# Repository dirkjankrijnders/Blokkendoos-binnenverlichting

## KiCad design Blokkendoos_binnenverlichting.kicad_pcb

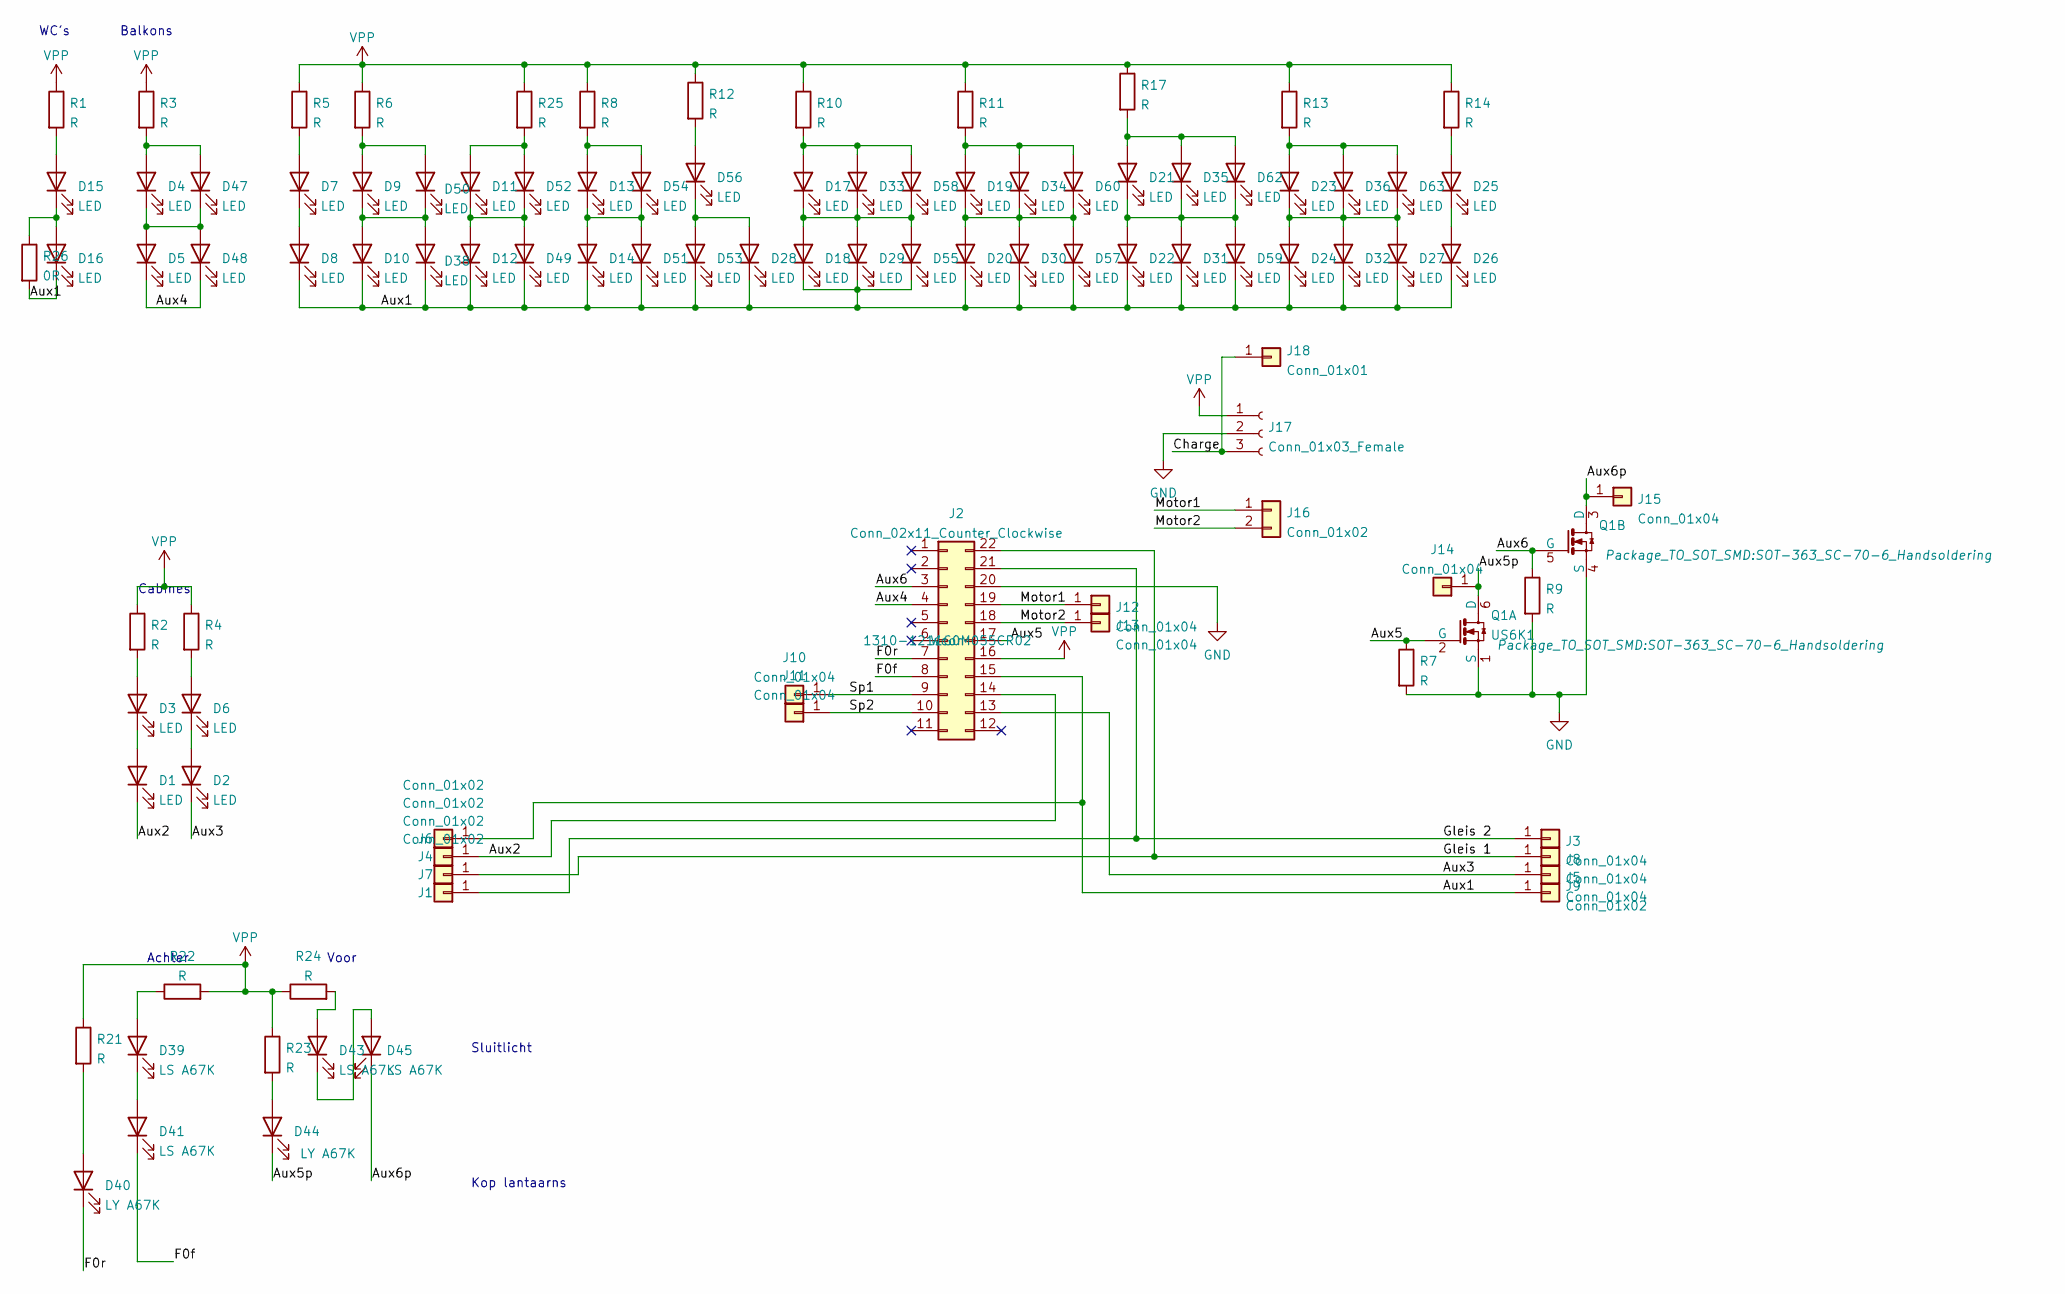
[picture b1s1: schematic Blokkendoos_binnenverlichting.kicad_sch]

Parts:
D1, D2, D3, D4, D5, D6, D7, D8, D9, D10, D11, D12, D13, D14, D15, D16, D17, D18, D19, D20, D21, D22, D23, D24, D25, D26, D27, D28, D29, D30, D31, D32, D33, D34, D35, D36, D38, D47, D48, D49, D50, D51, D52, D53, D54, D55, D56, D57, D58, D59, D60, D62, D63: LED; MHT151CYCT
D39, D41, D43, D45: LS A67K; LED_Osram_LY_A64K; MPN LS A67K-J1L2-1-0-2-R33-Z; LCSC C2830540
D40, D44: LY A67K; LED_Osram_LY_A64K; MPN LY A67K-J2M1-26-0-2-R33-Z; LCSC C2900136
J1, J4, J6, J7, J9: Conn_01x02; TestPoint_Pad_1.0x1.0mm
J2: Conn_02x11_Counter_Clockwise; PinHeader_2x11_P1.27mm_Vertical_SMD; LCSC C920913
J3, J5, J8, J10, J11, J12, J13, J14, J15: Conn_01x04; TestPoint_Pad_1.0x1.0mm
J16: Conn_01x02; Blokkendoos motor spings
J17: Conn_01x03_Female; PinHeader_1x03_P2.54mm_Horizontal
J18: Conn_01x01; PinHeader_1x01_P2.54mm_Horizontal
Q1: US6K1; SOT-363_SC-70-6_Handsoldering; LCSC2 C703686
R1, R2, R3, R4, R5, R6, R7, R8, R9, R10, R11, R12, R13, R14, R17, R21, R22, R23, R24, R25: R; R_0805_2012Metric_Pad1.20x1.40mm_HandSolder
R26: 0R; R_0805_2012Metric_Pad1.20x1.40mm_HandSolder

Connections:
/Aux1: D8.1 (K), D10.1 (K), D12.1 (K), D14.1 (K), D16.1 (K), D18.1 (K), D20.1 (K), D22.1 (K), D24.1 (K), D26.1 (K), D27.1 (K), D28.1 (K), D29.1 (K), D30.1 (K), D31.1 (K), D32.1 (K), D38.1 (K), D49.1 (K), D51.1 (K), D53.1 (K), D55.1 (K), D57.1 (K), D59.1 (K), J2.15, J6.1, J9.1, R26.2
/Aux2: D1.1 (K), J2.14, J4.1
/Aux3: D2.1 (K), J2.13, J5.1
/Aux4: D5.1 (K), D48.1 (K), J2.4
/Aux5: J2.17, Q1.2 (G), R7.1
/Aux5p: D44.1 (K), J14.1, Q1.6 (D)
/Aux6: J2.3, Q1.5 (G), R9.1
/Aux6p: D45.1 (K), J15.1, Q1.3 (D)
/Charge: J17.3, J18.1
/F0f: D41.1 (K), J2.8
/F0r: D40.1 (K), J2.7
/Gleis 1: J2.22, J7.1, J8.1
/Gleis 2: J1.1, J2.21, J3.1
/Motor1: J2.19, J12.1, J16.1
/Motor2: J2.18, J13.1, J16.2
/Sp1: J2.9, J10.1
/Sp2: J2.10, J11.1
GND: J2.20, J17.2, Q1.1 (S), Q1.4 (S), R7.2, R9.2
unnamed: D1.2 (A), D3.1 (K)
unnamed: D2.2 (A), D6.1 (K)
unnamed: D3.2 (A), R2.2
unnamed: D4.1 (K), D5.2 (A), D47.1 (K), D48.2 (A)
unnamed: D4.2 (A), D47.2 (A), R3.2
unnamed: D6.2 (A), R4.2
unnamed: D7.1 (K), D8.2 (A)
unnamed: D7.2 (A), R5.2
unnamed: D9.1 (K), D10.2 (A), D38.2 (A), D50.1 (K)
unnamed: D11.1 (K), D12.2 (A), D49.2 (A), D52.1 (K)
unnamed: D11.2 (A), D52.2 (A), R25.2
unnamed: D13.1 (K), D14.2 (A), D51.2 (A), D54.1 (K)
unnamed: D13.2 (A), D54.2 (A), R8.2
unnamed: D15.1 (K), D16.2 (A), R26.1
unnamed: D15.2 (A), R1.2
unnamed: D17.1 (K), D18.2 (A), D29.2 (A), D33.1 (K), D55.2 (A), D58.1 (K)
unnamed: D17.2 (A), D33.2 (A), D58.2 (A), R10.2
unnamed: D19.1 (K), D20.2 (A), D30.2 (A), D34.1 (K), D57.2 (A), D60.1 (K)
unnamed: D19.2 (A), D34.2 (A), D60.2 (A), R11.2
unnamed: D21.1 (K), D22.2 (A), D31.2 (A), D35.1 (K), D59.2 (A), D62.1 (K)
unnamed: D21.2 (A), D35.2 (A), D62.2 (A), R17.2
unnamed: D23.1 (K), D24.2 (A), D27.2 (A), D32.2 (A), D36.1 (K), D63.1 (K)
unnamed: D23.2 (A), D36.2 (A), D63.2 (A), R13.2
unnamed: D25.1 (K), D26.2 (A)
unnamed: D25.2 (A), R14.2
unnamed: D28.2 (A), D53.2 (A), D56.1 (K)
unnamed: D39.1 (K), D41.2 (A)
unnamed: D39.2 (A), R22.1
unnamed: D40.2 (A), R21.2
unnamed: D43.1 (K), D45.2 (A)
unnamed: D43.2 (A), R24.2
unnamed: D44.2 (A), R23.2
unnamed: D9.2 (A), D50.2 (A), R6.2
unnamed: D56.2 (A), R12.2
VPP: J2.16, J17.1, R1.1, R2.1, R3.1, R4.1, R5.1, R6.1, R8.1, R10.1, R11.1, R12.1, R13.1, R14.1, R17.1, R21.1, R22.2, R23.1, R24.1, R25.1

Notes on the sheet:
Sluitlicht
Kop lantaarns
Achter
WC's
Balkons
Cabines
Voor

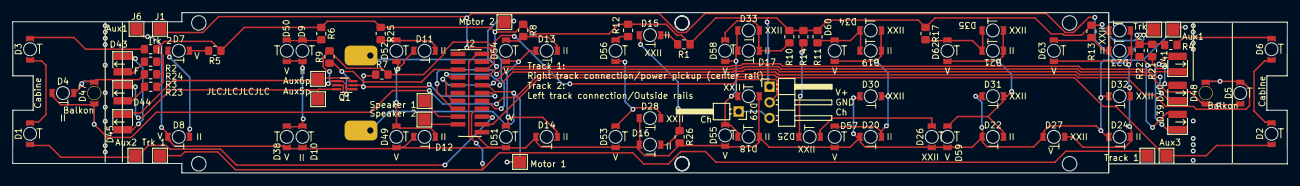
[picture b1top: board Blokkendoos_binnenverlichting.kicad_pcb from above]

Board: 2 copper layers, 206.8 x 26.0 mm, 99 parts (0 on the bottom side), 53 nets.

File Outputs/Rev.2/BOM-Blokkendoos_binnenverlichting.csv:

Comment,Designator,Footprint,LCSC
LS A67K,"D39,D41,D43,D45",LED_Osram_LY_A64K,C2830540
US6K1,Q1,SOT-363_SC-70-6_Handsoldering,C703686
Conn_02x11_Counter_Clockwise,J2,PinHeader_2x11_P1.27mm_Vertical_SMD,C920913
LED,D13,MHT151CYCT,
R,R21,R_0805_2012Metric_Pad1.20x1.40mm_HandSolder,
LED,D19,MHT151CYCT,
R,R12,R_0805_2012Metric_Pad1.20x1.40mm_HandSolder,
LED,D10,MHT151CYCT,
R,R7,R_0805_2012Metric_Pad1.20x1.40mm_HandSolder,
LED,D51,MHT151CYCT,
LED,D38,MHT151CYCT,
Conn_01x03_Female,J17,PinHeader_1x03_P2.54mm_Horizontal,
LED,D17,MHT151CYCT,
R,R2,R_0805_2012Metric_Pad1.20x1.40mm_HandSolder,
LED,D32,MHT151CYCT,
LED,D9,MHT151CYCT,
R,R23,R_0805_2012Metric_Pad1.20x1.40mm_HandSolder,
LED,D27,MHT151CYCT,
LED,D18,MHT151CYCT,
R,R1,R_0805_2012Metric_Pad1.20x1.40mm_HandSolder,
LED,D14,MHT151CYCT,
LED,D6,MHT151CYCT,
LED,D36,MHT151CYCT,
LY A67K,D40,LED_Osram_LY_A64K,
Conn_01x02,J16,Blokkendoos motor spings,
R,R5,R_0805_2012Metric_Pad1.20x1.40mm_HandSolder,
0R,R26,R_0805_2012Metric_Pad1.20x1.40mm_HandSolder,
R,R4,R_0805_2012Metric_Pad1.20x1.40mm_HandSolder,
LED,D24,MHT151CYCT,
LED,D62,MHT151CYCT,
LED,D12,MHT151CYCT,
LED,D33,MHT151CYCT,
LED,D22,MHT151CYCT,
LED,D3,MHT151CYCT,
LED,D8,MHT151CYCT,
LED,D28,MHT151CYCT,
LED,D31,MHT151CYCT,
R,R25,R_0805_2012Metric_Pad1.20x1.40mm_HandSolder,
LED,D49,MHT151CYCT,
R,R8,R_0805_2012Metric_Pad1.20x1.40mm_HandSolder,
LED,D63,MHT151CYCT,
LED,D11,MHT151CYCT,
LED,D60,MHT151CYCT,
LED,D34,MHT151CYCT,
R,R6,R_0805_2012Metric_Pad1.20x1.40mm_HandSolder,
LED,D57,MHT151CYCT,
LED,D30,MHT151CYCT,
R,R22,R_0805_2012Metric_Pad1.20x1.40mm_HandSolder,
LED,D5,MHT151CYCT,
LED,D25,MHT151CYCT,
LED,D1,MHT151CYCT,
LED,D4,MHT151CYCT,
LED,D21,MHT151CYCT,
LED,D20,MHT151CYCT,
LED,D53,MHT151CYCT,
R,R3,R_0805_2012Metric_Pad1.20x1.40mm_HandSolder,
LED,D47,MHT151CYCT_dual_side,
Conn_01x01,J18,PinHeader_1x01_P2.54mm_Horizontal,
LED,D48,MHT151CYCT_dual_side,
R,R9,R_0805_2012Metric_Pad1.20x1.40mm_HandSolder,
LED,D50,MHT151CYCT,
LED,D26,MHT151CYCT,
LED,D35,MHT151CYCT,
LY A67K,D44,LED_Osram_LY_A64K,
LED,D52,MHT151CYCT,
LED,D2,MHT151CYCT,
LED,D7,MHT151CYCT,
R,R11,R_0805_2012Metric_Pad1.20x1.40mm_HandSolder,
LED,D23,MHT151CYCT,
LED,D29,MHT151CYCT,
LED,D54,MHT151CYCT,
LED,D15,MHT151CYCT,
R,R13,R_0805_2012Metric_Pad1.20x1.40mm_HandSolder,
R,R10,R_0805_2012Metric_Pad1.20x1.40mm_HandSolder,
LED,D56,MHT151CYCT,
LED,D58,MHT151CYCT,
R,R24,R_0805_2012Metric_Pad1.20x1.40mm_HandSolder,
R,R14,R_0805_2012Metric_Pad1.20x1.40mm_HandSolder,
R,R17,R_0805_2012Metric_Pad1.20x1.40mm_HandSolder,
LED,D59,MHT151CYCT,
LED,D55,MHT151CYCT,
LED,D16,MHT151CYCT,

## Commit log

2022-02-28 JCLPCB order
2022-03-25 Added Rev 0 production files
2022-03-25 Added light guide mount
2022-03-26 Fixed all milestone 1 issues to date
2022-03-26 Holes for motor wires
2022-11-13 Removed plating on reverse mounted LED's, close #13
2022-12-11 Marked the LED orientation on the silkscreen
2022-12-11 Added powerpack schematic
2022-12-11 Fixed mounting hole locations and sizes, closes #8
2022-12-11 Moved motor car mounting holes, closes #7
2022-12-11 Moved front and rear light, closes #14, moved x less then 1.4 mm, that seems too much.
2022-12-11 Replaced FDC6303 with US6K1 in schematic
2022-12-11 Removed powerpack hardware, should be on separate PCB. Replaced FDC6303, closes #12
2022-12-11 Added motor spring mount pads, closes #9
2022-12-11 Pulled traces away from edge, making room to cut the corners and/or PCB to shape. Closes #11.
2022-12-11 Added connectors for powerpack and DRC passes, except for silkscreen
2022-12-12 Silkscreen fixes, closes #10
2023-01-14 Added production files for first and second revision.
